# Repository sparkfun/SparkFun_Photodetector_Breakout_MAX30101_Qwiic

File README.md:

SparkFun Photodetector Breakout - MAX30101 (Qwiic)
========================================

[*SparkFun Photodetector Breakout - MAX30101 (Qwiic) (SEN-16474)*](https://www.sparkfun.com/products/16474)

This updated version of the [SparkFun Particle Sensor Breakout](https://www.sparkfun.com/products/14045) includes the MAX30101, a highly sensitive optical sensor and successor to the MAX30105 and MAX30102. The MAX30101 includes three LEDs and an optical detector in a single package. The operating principle behind the sensor, utilizes the photon detector to measure the amount of light that is reflected back from the light being emitted by the LEDs. This is useful for various applications like particle (*i.e. smoke*) detection, proximity measurements, and even [photoplethysmography](https://en.wikipedia.org/wiki/Photoplethysmogram). For more accurate and reliable biometric readings, we recommend the [SparkFun Pulse Oximeter and Heart Rate Sensor](https://www.sparkfun.com/products/15219), which utilizes proprietary algorithms programmed on the MAX32664 Biometric Sensor Hub.

<div class="alert alert-danger"><a href="https://www.sparkfun.com/terms"><b>&#9760; NOTE:</b> Our products are <b><u>NOT</u></b> intended to diagnose or treat any conditions and in life saving applications.</a></div>

Repository Contents
-------------------

* **/Documentation** - Data sheets, additional product information
* **/Hardware** - Eagle design files (.brd, .sch)
* **/Hardware/Production** - Production panel files and gerbers (.brd)

Documentation
--------------

* **[Hookup Guide](https://learn.sparkfun.com/tutorials/sparkfun-photodetector-max30101-hookup-guide)** - Basic hookup guide for the SparkFun Photodetector Breakout - MAX30101 (Qwiic).
* **[Python Package](https://github.com/sparkfun/Qwiic_MAX3010x_Py)** - Python package with examples. Pip and Pip3 install supported!!
* **[Arduino Library](https://github.com/sparkfun/SparkFun_MAX3010x_Sensor_Library)** - Basic Arduino Library for the SparkFun Photodetector Breakout - MAX30101 (Qwiic).

License Information
-------------------

This product is _**open source**_! 

Please review the LICENSE.md file for license information. 

If you have any questions or concerns on licensing, please contact technical support on our [SparkFun forums](https://forum.sparkfun.com/viewforum.php?f=152).

Distributed as-is; no warranty is given.

- Your friends at SparkFun.

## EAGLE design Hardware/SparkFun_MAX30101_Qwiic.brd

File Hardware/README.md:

SparkFun Particle Sensor MAX30101 (Qwiic) Design Files
=====================================

The .sch and .brd files hare are Eagle CAD schematic and PCB design files from SparkFun Electronics.
A freeware version of Eagle can be found [here](https://www.autodesk.com/products/eagle/free-download).

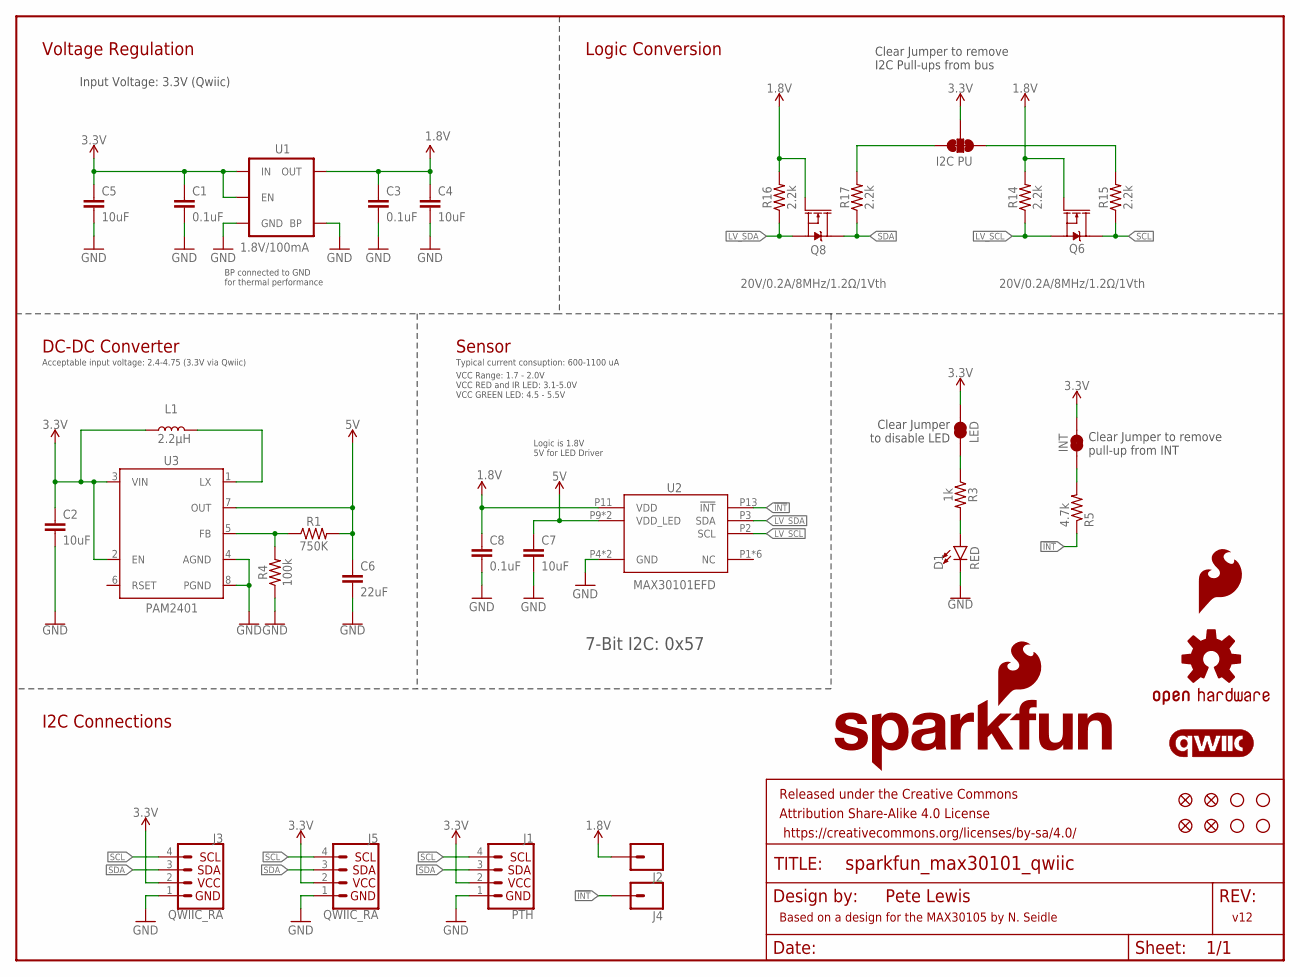
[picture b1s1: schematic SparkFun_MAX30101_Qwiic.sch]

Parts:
C1, C3, C8: 0.1uF; 0402
C2, C4, C5, C7: 10uF; 0603
C6: 22uF; 0805
D1: RED; LED-0603
FID1, FID2, FID3, FID4: FIDUCIAL1X2; FIDUCIAL-1X2
FRAME1: FRAME-LETTER; CREATIVE_COMMONS
J1: PTH; 1X04_NO_SILK
J2, J4: CONN_01PTH_NO_SILK_YES_STOP; 1X01_NO_SILK
J3, J5: QWIIC_RA; JST04_1MM_RA
JP1: LED; SMT-JUMPER_2_NC_TRACE_SILK
JP2: INT; SMT-JUMPER_2_NC_TRACE_SILK
JP4: I2C PU; SMT-JUMPER_3_2-NC_TRACE_SILK
L1: 2.2μH; 0806
LOGO1: SFE_LOGO_NAME_FLAME.1_INCH; SFE_LOGO_NAME_FLAME_.1
LOGO2: OSHW-LOGOS; OSHW-LOGO-S
LOGO3: QWIIC_LOGO_5MM; QWIIC_5MM
LOGO4: SFE_LOGO_FLAME.1_INCH; SFE_LOGO_FLAME_.1
Q6, Q8: 20V/0.2A/8MHz/1.2Ω/1Vth; SOT-416FL
R1: 750K; 0603
R3: 1k; 0603
R4: 100k; 0603
R5: 4.7k; 0603
R14, R15, R16, R17: 2.2k; 0603
STANDOFF1, STANDOFF2, STANDOFF3, STANDOFF4: STAND-OFF
U1: 1.8V/100mA; SC70
U2: MAX30101EFD; 14_PIN_OESIP
U3: PAM2401; MSOP8

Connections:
1.8V: C3.1, C4.1, C8.1, J2.1, Q6.1 (G), Q8.1 (G), R14.2, R16.2, U1.5 (OUT), U2.P11 (VDD)
3.3V: C1.1, C2.1, C5.1, J1.2, J3.2, J5.2, JP1.2, JP2.2, JP4.2, L1.1, U1.1 (IN), U1.3 (EN), U3.2 (EN), U3.3 (VIN)
5V: C6.1, C7.1, R1.2, U2.P9 (VDD_LED), U2.P10 (VDD_LED), U3.7 (OUT)
!INT: J4.1, R5.1, U2.P13 (!INT)
GND: C1.2, C2.2, C3.2, C4.2, C5.2, C6.2, C7.2, C8.2, D1.C, J1.1, J3.1, J5.1, R4.1, U1.2 (GND), U1.4 (BP), U2.P4 (GND), U2.P12 (GND), U3.4 (AGND), U3.8 (PGND)
LV_SCL: Q6.2 (S), R14.1, U2.P2 (SCL)
LV_SDA: Q8.2 (S), R16.1, U2.P3 (SDA)
unnamed: JP2.1, R5.2
unnamed: R1.1, R4.2, U3.5 (FB)
unnamed: L1.2, U3.1 (LX)
unnamed: D1.A, R3.2
unnamed: JP4.3, R15.2
unnamed: JP4.1, R17.2
unnamed: JP1.1, R3.1
SCL: J1.4, J3.4, J5.4, Q6.3 (D), R15.1
SDA: J1.3, J3.3, J5.3, Q8.3 (D), R17.1

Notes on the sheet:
7-Bit I2C: 0x57
v12
Pete Lewis
Voltage Regulation
Logic Conversion
Sensor
Input Voltage: 3.3V (Qwiic)
Clear Jumper to remove I2C Pull-ups from bus
Clear Jumper to remove pull-up from INT
Logic is 1.8V 5V for LED Driver
BP connected to GND for thermal performance
I2C Connections
Based on a design for the MAX30105 by N. Seidle
Clear Jumper to disable LED
DC-DC Converter
Typical current consuption: 600-1100 uA
VCC Range: 1.7 - 2.0V VCC RED and IR LED: 3.1-5.0V VCC GREEN LED: 4.5 - 5.5V
Acceptable input voltage: 2.4-4.75 (3.3V via Qwiic)

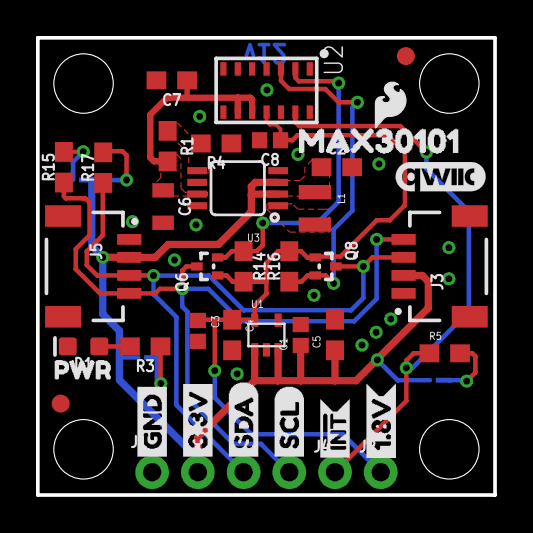
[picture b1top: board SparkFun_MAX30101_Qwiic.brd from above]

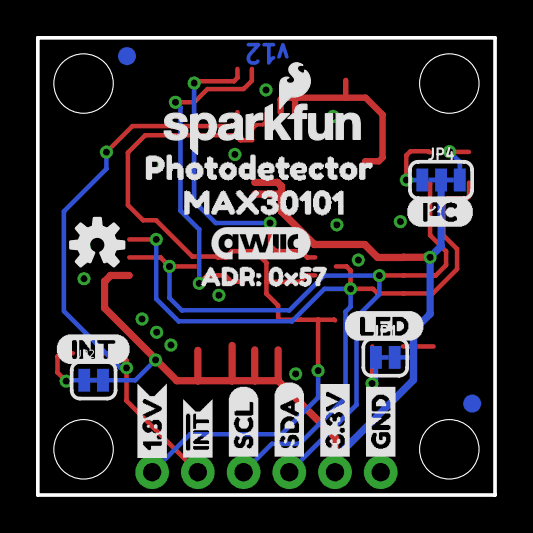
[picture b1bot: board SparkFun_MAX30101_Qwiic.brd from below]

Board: 2 copper layers, 25.4 x 25.4 mm, 65 parts (20 on the bottom side), 16 nets.

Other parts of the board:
U$1: PHOTODETECTOR3
U$3, U$11: INT#-[<-04
U$4, U$24: MAX301010
U$7: INT-()-04
U$8: LED0
U$9, U$12: SCL-[)
U$10, U$23: GND-04
U$13, U$14: SDA-[)
U$15: ADR#_0X570
U$16: QWIIC_5.5MM
U$19, U$22: 3.3V
U$20, U$27: 1#8V0
U$21: I_SUPER2_C-()-04
U$26: PWR_TO

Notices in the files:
parts and their libraries:
SparkFun-Aesthetics: Licensing: CC v3.0 Share-Alike You are welcome to use this library for commercial purposes.
SparkFun-Resistors: Licensing: Creative Commons ShareAlike 4.0 International - https://creativecommons.org/licenses/by-sa/4.0
SparkFun-Aesthetics: Released under the Creative Commons
